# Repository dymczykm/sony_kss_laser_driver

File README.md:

# Sony KSS laser pickup driver

This board is used to drive the KSS-family pickups (KSS-16x, KSS-220 etc.) with a circuit very similar to one used by various kinds of mobile and home players, which all used the CXA1081 IC. Personally, I've used this circuit to measure/adjust the laser diode current and to measure the light emission (using a Leader LPM-8000 meter). A separate circuit like this one makes it much easier to handle the pickup compared to working within cramped Discman or car audio players.

The circuit is pretty much a copy of the Alpine 7909 design, but very closely resembles Discmans (such as D-33) from that era. The only difference I've noticed is the resistor for the `VR` line - it's 0-ohm in 7909, but 91-ohm in some of the Discman implementations.

The circuit is tested and worked fine on several Sony pickups without burning any of them :) Still, you use it at your own risk.

## Potentially compatible devices/pickups

### Sony Discmans
- KSS-220A (D-11, D-22, D-33, D-99, D-800K, D-802K)
- KSS-162A (D-4, D-12, D-20, D-T20, D-30, D-34, D-40, D-55T, D-90, D-100)

### Car audio
- Alpine 7909 (KSS-163A)
- Sony CDX-5080 CDX-7580 CDX-R77 CDX-R79 (KSS-168A)
- Blaupunkt CD42 family
- Blaupunkt New York SCD08 (KSS-164A), BMW Bavaria ELECTRONIC CD (II)

## Connections

### Power supply
Connect to `J1` a stable power source within the range acceptable by `78L05` used in the circuit.

### Laser pickup
You can use either of the 3 connections:
- 1mm pitch FFC connector,
- 1.25mm pitch FFC conector,
- solder pads (`PD` - monitor diode, `LD` - laser diode, `GND` - ground); please mind the ESD measures.

The `LD_SHORT` jumper shorts out the laser diode. Remove the jumper once your pickup is fully connected.

### Switching on the laser diode

Use the `SW1` switch to turn on the diode. After turning it on, do not look directly into it lens.

### Measuring laser diode current

You can measure the laser current on the `J2`/`J3` banana jacks as a voltage across a 10-ohm resistor.

## CXA1081 symbol/footprint

You can find it in [my library](https://github.com/dymczykm/marcin_kicad_library).

CXA1081 has a Samsung equivalent (KA9201) and its [datasheet is hosted by console5.com](https://console5.com/techwiki/images/a/a1/KA9201.pdf).

## Component list

I've sourced CXA1081 SDIP from ebay (I took a used one to be sure it's not a counterfeit).

Most other components are listed in the [CSV file](digikey_bom.csv). Please note that it does not contain components I had already at hand, so double check it against the schematic.

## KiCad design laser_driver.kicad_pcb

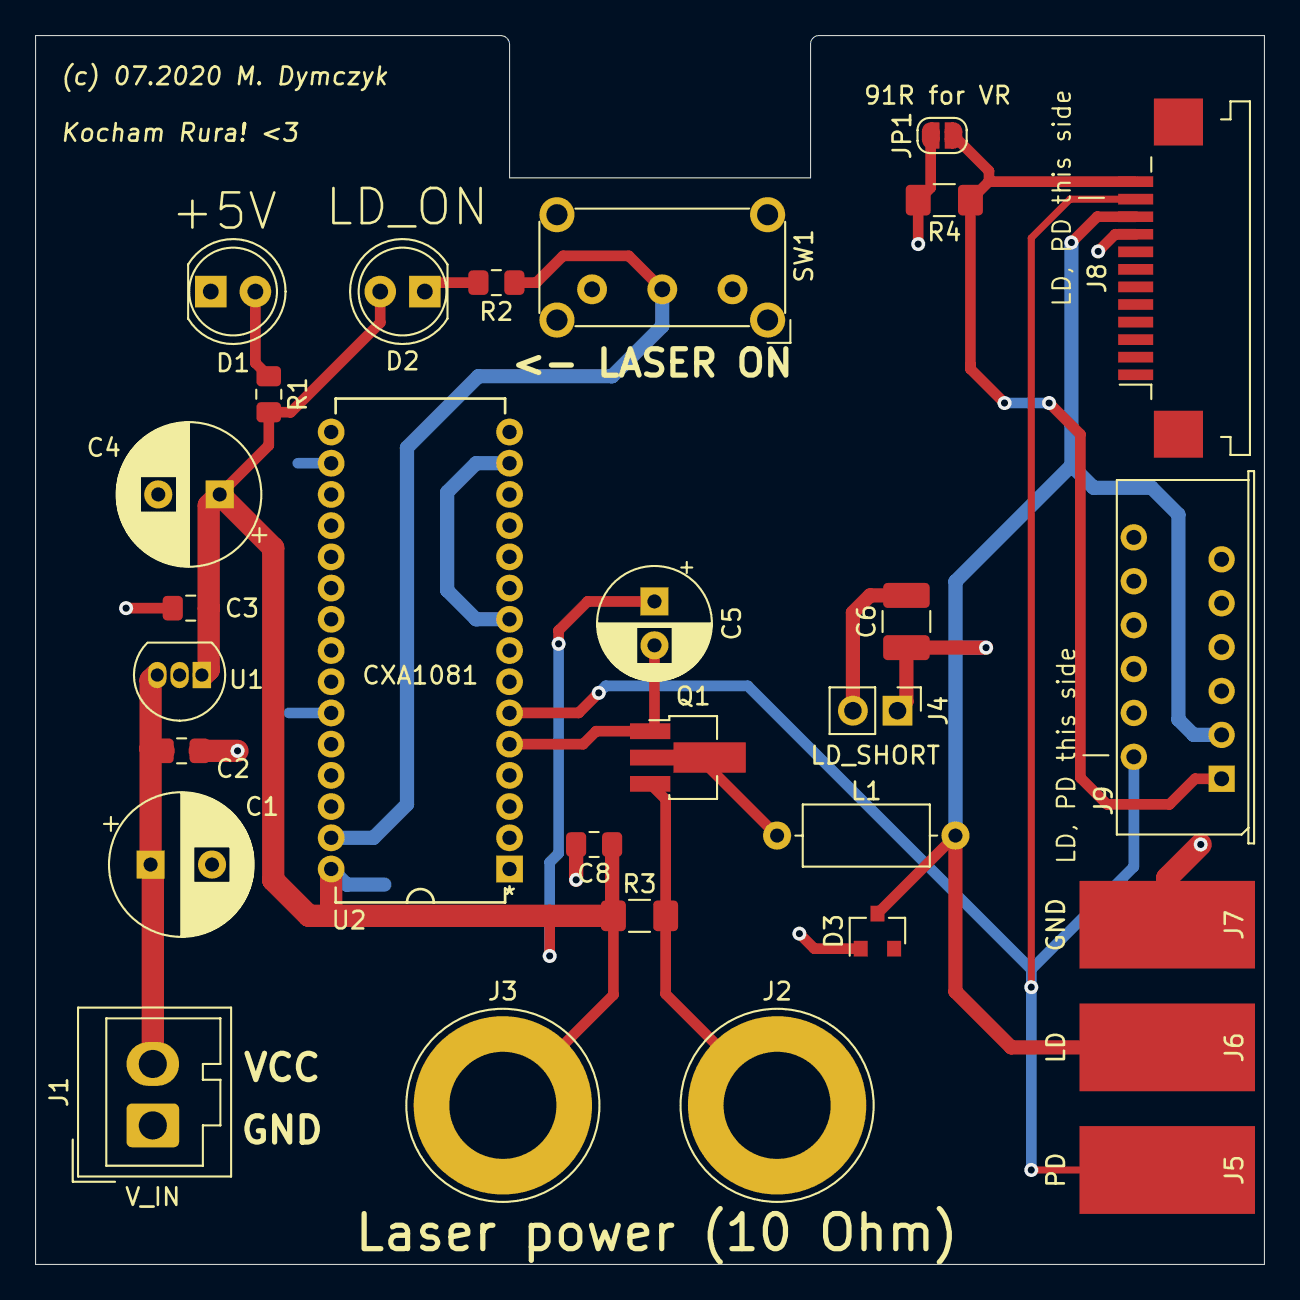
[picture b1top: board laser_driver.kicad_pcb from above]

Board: 2 copper layers, 70.0 x 70.0 mm, 30 parts (1 on the bottom side), 13 nets.

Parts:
C1, C4: 100u; CP_Radial_D8.0mm_P3.50mm
C2, C3, C7, C8: 100n; C_0805_2012Metric_Pad1.15x1.40mm_HandSolder
C5: 47u/4v; CP_Radial_D6.3mm_P2.50mm
C6: 1u/10; C_1210_3225Metric_Pad1.42x2.65mm_HandSolder
D1: +5V; LED_D5.0mm
D2: LD_ON; LED_D5.0mm
D3: M1MA151KT1G; D_SOT-23_ANK
J1: V_IN; Wago_734-132_1x02_P3.50mm_Vertical
J2: Laser; Banana_Jack_1Pin
J3: Power; Banana_Jack_1Pin
J4: LD_SHORT; PinHeader_1x02_P2.54mm_Vertical
J5: PD; SolderWirePad_1x01_SMD_5x10mm
J6: LD; SolderWirePad_1x01_SMD_5x10mm
J7: GND; SolderWirePad_1x01_SMD_5x10mm
J8: 1mm; Molex_0522071233
J9: 1.25mm; Molex_0039532124
JP1: VR; SolderJumper-2_P1.3mm_Open_RoundedPad1.0x1.5mm
L1: 10u; L_Axial_L7.0mm_D3.3mm_P10.16mm_Horizontal_Fastron_MICC
Q1: Q_PNP_BCE; SOT-89-3_Handsoldering
R1, R2: 220; R_0805_2012Metric_Pad1.15x1.40mm_HandSolder
R3: 10 0.1%; R_1206_3216Metric_Pad1.42x1.75mm_HandSolder
R4: 91; R_1206_3216Metric_Pad1.42x1.75mm_HandSolder
SW1: SW_SPDT; SW_E-Switch_EG1224_SPDT_Angled
U1: L78L05_TO92; TO-92_Inline
U2: CXA1081; SDIP30

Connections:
+5V: C3.1, C4.1, C5.1, C7.2, C8.1, D2.2, J3.1, R1.2, R3.1, U1.1, U2.30
GND: C1.2, C2.2, C3.2, C4.2, C6.2, C7.1, C8.2, D1.1, D3.2, J1.1, J4.2, J7.1, J8.9, J9.4, JP1.1, R4.2, SW1.3, U1.2, U2.17, U2.25
unnamed: C1.1, C2.1, J1.2, U1.3
unnamed: C5.2, Q1.1, U2.5
unnamed: C6.1, D3.1, J4.1, J6.1, J8.10, J9.3, L1.2
unnamed: D1.2, R1.1
unnamed: D2.1, R2.2
unnamed: J2.1, Q1.3, R3.2
unnamed: J5.1, J8.11, J9.2, U2.6
unnamed: J8.12, J9.1, JP1.2, R4.1
unnamed: L1.1, Q1.2
unnamed: R2.1, SW1.2, U2.29
unnamed: U2.9, U2.14

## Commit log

2020-12-28 Add files and the readme.
2020-12-28 Add a note about the switch.
2020-12-28 Minor.
2020-12-28 Add a link do the CXA1081 datasheet.

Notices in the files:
parts and their libraries:
Copyright 2016 Accelerated Designs. All rights reserved.
